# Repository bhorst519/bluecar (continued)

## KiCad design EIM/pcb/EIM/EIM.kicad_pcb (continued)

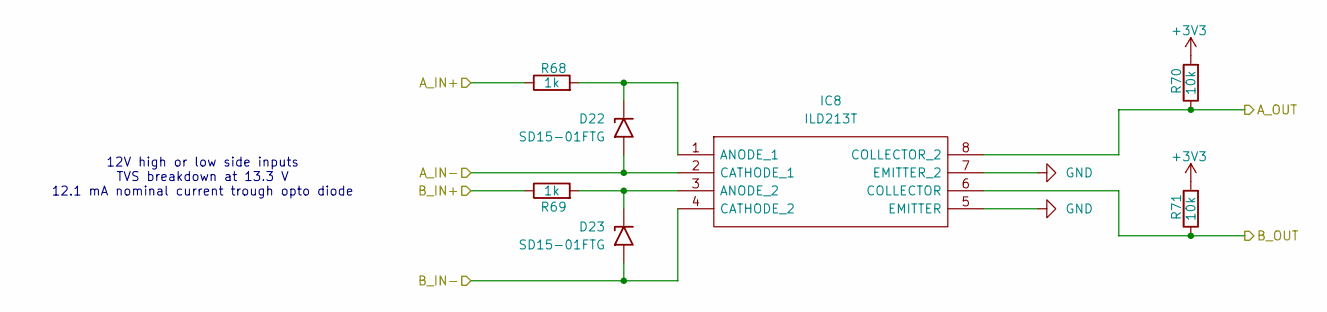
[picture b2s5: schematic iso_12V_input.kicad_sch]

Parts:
D22, D23: SD15-01FTG; D_SOD-323
IC8: ILD213T; SOIC127P610X350-8N; Mouser Part Number 782-ILD213T
R68, R69: 1k; R_0805_2012Metric_Pad1.20x1.40mm_HandSolder
R70, R71: 10k; R_0805_2012Metric_Pad1.20x1.40mm_HandSolder

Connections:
+3V3: R70.2, R71.2; also elsewhere on the board
+12V: R68.1, R69.1; also elsewhere on the board
/5TH: D23.2 (A2), IC8.4 (CATHODE_2); also elsewhere on the board
/5TH_MCU: IC8.6 (COLLECTOR), R71.1; also elsewhere on the board
/6TH: D22.2 (A2), IC8.2 (CATHODE_1); also elsewhere on the board
/6TH_MCU: IC8.8 (COLLECTOR_2), R70.1; also elsewhere on the board
GND: IC8.5 (EMITTER), IC8.7 (EMITTER_2); also elsewhere on the board
unnamed: D22.1 (A1), IC8.1 (ANODE_1), R68.2
unnamed: D23.1 (A1), IC8.3 (ANODE_2), R69.2

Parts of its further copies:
D13, D14, D16, D17, D18, D19, D20, D21, D24, D25, D30, D31: SD15-01FTG; D_SOD-323
IC3, IC5, IC6, IC7, IC9, IC10: ILD213T; SOIC127P610X350-8N; Mouser Part Number 782-ILD213T
R22, R23, R56, R57, R60, R61, R64, R65, R72, R73, R89, R90: 1k; R_0805_2012Metric_Pad1.20x1.40mm_HandSolder
R24, R25, R58, R59, R62, R63, R66, R67, R74, R75, R91, R92: 10k; R_0805_2012Metric_Pad1.20x1.40mm_HandSolder

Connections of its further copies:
+3V3: R24.2, R25.2, R58.2, R59.2, R62.2, R63.2, R66.2, R67.2, R74.2, R75.2, R91.2, R92.2; also elsewhere on the board
+12V: R23.1, R60.1, R61.1, R64.1, R65.1, R72.1, R73.1; also elsewhere on the board
/1ST: D19.2 (A2), IC6.4 (CATHODE_2); also elsewhere on the board
/1ST_MCU: IC6.6 (COLLECTOR), R63.1; also elsewhere on the board
/2ND: D18.2 (A2), IC6.2 (CATHODE_1); also elsewhere on the board
/2ND_MCU: IC6.8 (COLLECTOR_2), R62.1; also elsewhere on the board
/3RD: D21.2 (A2), IC7.4 (CATHODE_2); also elsewhere on the board
/3RD_MCU: IC7.6 (COLLECTOR), R67.1; also elsewhere on the board
/4TH: D20.2 (A2), IC7.2 (CATHODE_1); also elsewhere on the board
/4TH_MCU: IC7.8 (COLLECTOR_2), R66.1; also elsewhere on the board
/FAULT_IND: D24.2 (A2), IC9.2 (CATHODE_1); also elsewhere on the board
/FAULT_IND_MCU: IC9.8 (COLLECTOR_2), R74.1; also elsewhere on the board
/HIGHBEAM: R90.1; also elsewhere on the board
/HIGHBEAM_FEED: R89.1; also elsewhere on the board
/HIGHBEAM_MCU: IC10.6 (COLLECTOR), R92.1; also elsewhere on the board
/LOWBEAM_MCU: IC10.8 (COLLECTOR_2), R91.1; also elsewhere on the board
/NEUTRAL: D14.2 (A2), IC3.4 (CATHODE_2); also elsewhere on the board
/NEUTRAL_MCU: IC3.6 (COLLECTOR), R25.1; also elsewhere on the board
/OIL: D25.2 (A2), IC9.4 (CATHODE_2); also elsewhere on the board
/OIL_P_LOW_MCU: IC9.6 (COLLECTOR), R75.1; also elsewhere on the board
/TACH_MCU: IC3.8 (COLLECTOR_2), R24.1; also elsewhere on the board
/TA_SIG: R22.1; also elsewhere on the board
/TURN_L: R56.1; also elsewhere on the board
/TURN_L_MCU: IC5.8 (COLLECTOR_2), R58.1; also elsewhere on the board
/TURN_R: R57.1; also elsewhere on the board
/TURN_R_MCU: IC5.6 (COLLECTOR), R59.1; also elsewhere on the board
GND: D13.2 (A2), D16.2 (A2), D17.2 (A2), D30.2 (A2), D31.2 (A2), IC3.2 (CATHODE_1), IC3.5 (EMITTER), IC3.7 (EMITTER_2), IC5.2 (CATHODE_1), IC5.4 (CATHODE_2), IC5.5 (EMITTER), IC5.7 (EMITTER_2), IC6.5 (EMITTER), IC6.7 (EMITTER_2), IC7.5 (EMITTER), IC7.7 (EMITTER_2), IC9.5 (EMITTER), IC9.7 (EMITTER_2), IC10.2 (CATHODE_1), IC10.4 (CATHODE_2), IC10.5 (EMITTER), IC10.7 (EMITTER_2); also elsewhere on the board
unnamed: D13.1 (A1), IC3.1 (ANODE_1), R22.2
unnamed: D14.1 (A1), IC3.3 (ANODE_2), R23.2
unnamed: D16.1 (A1), IC5.1 (ANODE_1), R56.2
unnamed: D17.1 (A1), IC5.3 (ANODE_2), R57.2
unnamed: D18.1 (A1), IC6.1 (ANODE_1), R60.2
unnamed: D19.1 (A1), IC6.3 (ANODE_2), R61.2
unnamed: D20.1 (A1), IC7.1 (ANODE_1), R64.2
unnamed: D21.1 (A1), IC7.3 (ANODE_2), R65.2
unnamed: D24.1 (A1), IC9.1 (ANODE_1), R72.2
unnamed: D25.1 (A1), IC9.3 (ANODE_2), R73.2
unnamed: D30.1 (A1), IC10.1 (ANODE_1), R89.2
unnamed: D31.1 (A1), IC10.3 (ANODE_2), R90.2

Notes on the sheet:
12V high or low side inputs TVS breakdown at 13.3 V 12.1 mA nominal current trough opto diode

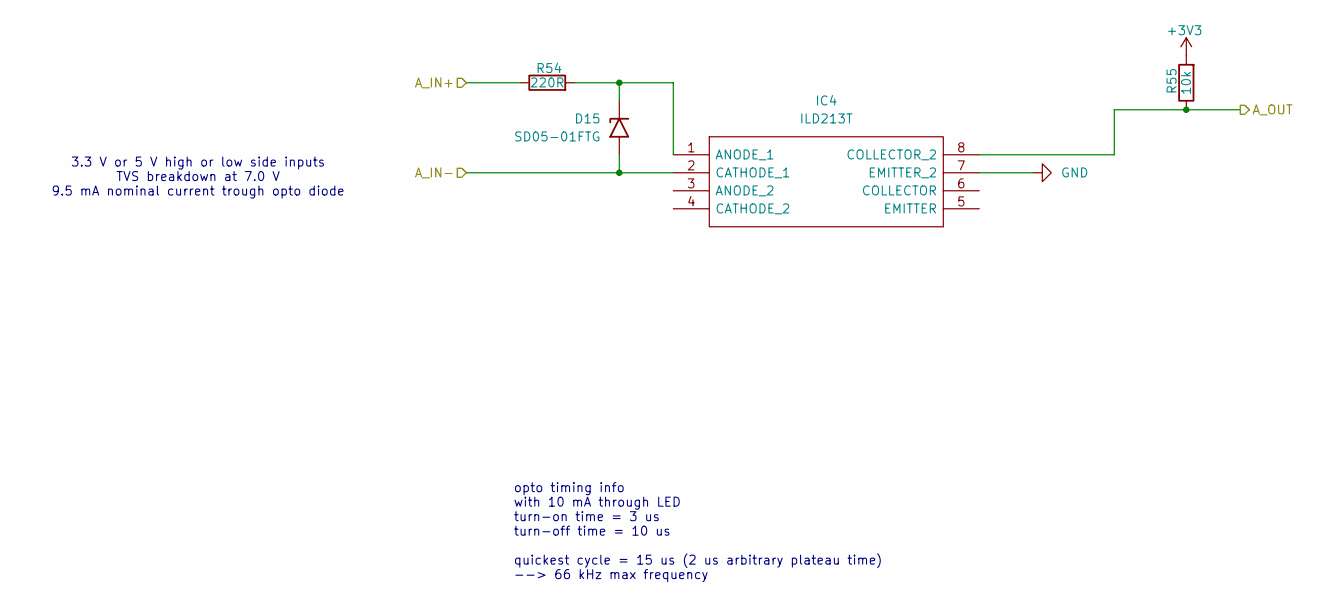
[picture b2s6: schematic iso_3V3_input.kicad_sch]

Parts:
D15: SD05-01FTG; D_SOD-323
IC4: ILD213T; SOIC127P610X350-8N; Mouser Part Number 782-ILD213T
R54: 220R; R_0805_2012Metric_Pad1.20x1.40mm_HandSolder
R55: 10k; R_0805_2012Metric_Pad1.20x1.40mm_HandSolder

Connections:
+3V3: R54.1, R55.2; also elsewhere on the board
/SP_SIG: D15.2 (A2), IC4.2 (CATHODE_1); also elsewhere on the board
/VSS_MCU: IC4.8 (COLLECTOR_2), R55.1; also elsewhere on the board
GND: IC4.7 (EMITTER_2); also elsewhere on the board
unnamed: D15.1 (A1), IC4.1 (ANODE_1), R54.2

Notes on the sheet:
3.3 V or 5 V high or low side inputs TVS breakdown at 7.0 V 9.5 mA nominal current trough opto diode
opto timing info with 10 mA through LED turn-on time = 3 us turn-off time = 10 us quickest cycle = 15 us (2 us arbitrary plateau time) --> 66 kHz max frequency

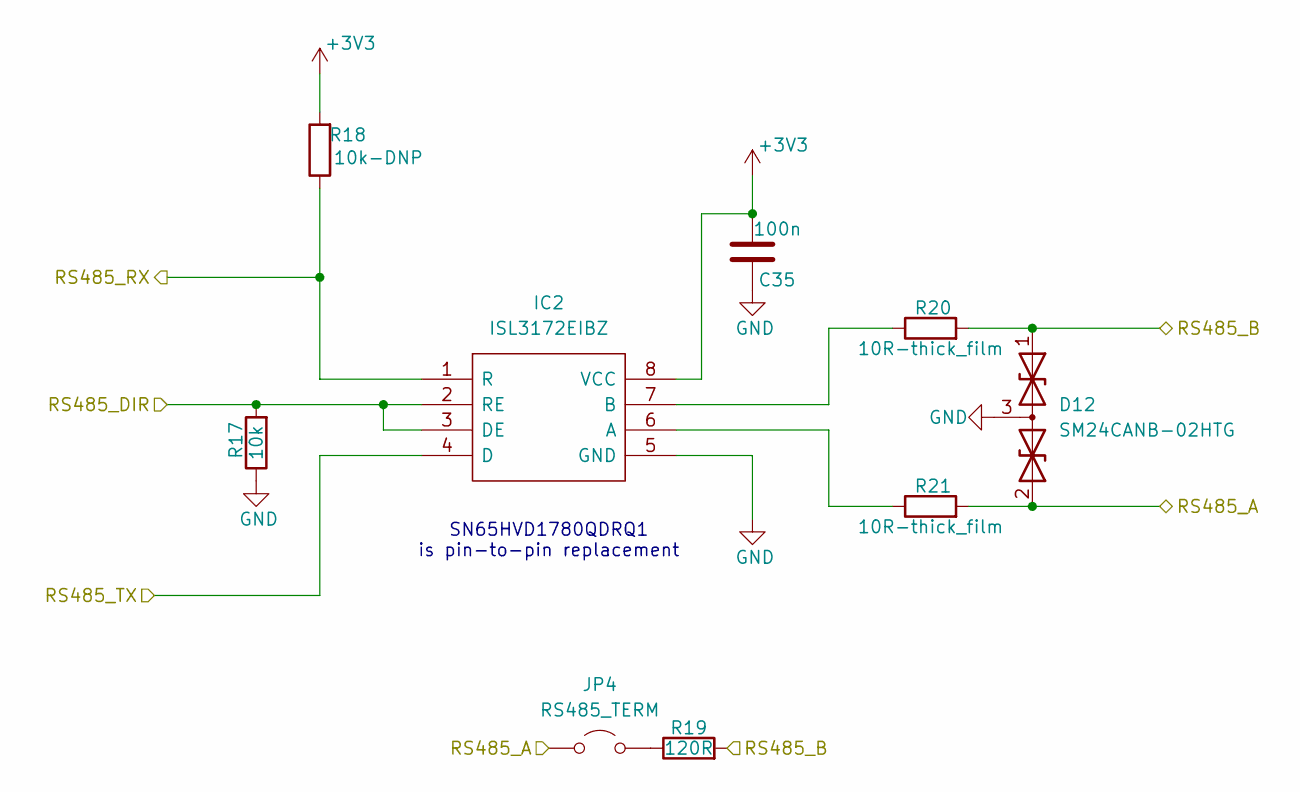
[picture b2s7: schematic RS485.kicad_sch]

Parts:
C35: 100n; C_0805_2012Metric_Pad1.18x1.45mm_HandSolder
D12: SM24CANB-02HTG; SOT-23-3
IC2: ISL3172EIBZ; SOIC-8_3.9x4.9mm_P1.27mm; Mouser Part Number 595-SN65HVD1780QDRQ1
JP4: RS485_TERM; SolderJumper-2_P1.3mm_Bridged_RoundedPad1.0x1.5mm
R17: 10k; R_0805_2012Metric_Pad1.20x1.40mm_HandSolder
R18: 10k-DNP; R_0805_2012Metric_Pad1.20x1.40mm_HandSolder
R19: 120R; R_0805_2012Metric_Pad1.20x1.40mm_HandSolder
R20, R21: 10R-thick_film; R_0805_2012Metric_Pad1.20x1.40mm_HandSolder

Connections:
+3V3: C35.1, IC2.8 (VCC), R18.2; also elsewhere on the board
/RS485_A: D12.2 (A2), JP4.1 (A), R21.2; also elsewhere on the board
/RS485_B: D12.1 (A1), R19.2, R20.2; also elsewhere on the board
/RS485_DIR: IC2.2 (RE), IC2.3 (DE), R17.2; also elsewhere on the board
/RS485_RX: IC2.1 (R), R18.1; also elsewhere on the board
/RS485_TX: IC2.4 (D); also elsewhere on the board
GND: C35.2, D12.3 (common), IC2.5 (GND), R17.1; also elsewhere on the board
unnamed: IC2.6 (A), R21.1
unnamed: IC2.7 (B), R20.1
unnamed: JP4.2 (B), R19.1

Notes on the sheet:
SN65HVD1780QDRQ1 is pin-to-pin replacement

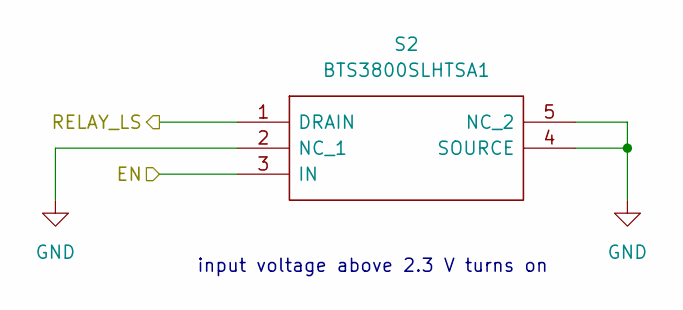
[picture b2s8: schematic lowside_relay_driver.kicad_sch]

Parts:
S2: BTS3800SLHTSA1; Mouser Part Number 726-BTS3800SLHTSA1

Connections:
/HEADLIGHT_RELAY: S2.1 (DRAIN); also elsewhere on the board
/HL_RLY_EN: S2.3 (IN); also elsewhere on the board
GND: S2.2 (NC_1), S2.4 (SOURCE), S2.5 (NC_2); also elsewhere on the board

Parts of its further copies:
S1, S3: BTS3800SLHTSA1; Mouser Part Number 726-BTS3800SLHTSA1

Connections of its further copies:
/LAP_RELAY: S3.1 (DRAIN); also elsewhere on the board
/LAP_RLY_EN: S3.3 (IN); also elsewhere on the board
/MAIN_RLY_COIL_LS: S1.1 (DRAIN); also elsewhere on the board
/MAIN_RLY_EN: S1.3 (IN); also elsewhere on the board
GND: S1.2 (NC_1), S1.4 (SOURCE), S1.5 (NC_2), S3.2 (NC_1), S3.4 (SOURCE), S3.5 (NC_2); also elsewhere on the board

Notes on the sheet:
input voltage above 2.3 V turns on

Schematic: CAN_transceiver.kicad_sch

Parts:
C30: 100n; C_0805_2012Metric_Pad1.18x1.45mm_HandSolder
D8: SM24CANB-02HTG; SOT-23-3
JP2: CAN_TERM; SolderJumper-2_P1.3mm_Open_RoundedPad1.0x1.5mm
R13: 120R; R_0805_2012Metric_Pad1.20x1.40mm_HandSolder
U3: SN65HVD233; SOIC-8_3.9x4.9mm_P1.27mm

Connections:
+3V3: C30.2, U3.3 (VCC); also elsewhere on the board
/CAN1_H: D8.1 (A1), JP2.1 (A), U3.7 (CANH); also elsewhere on the board
/CAN1_L: D8.2 (A2), R13.2, U3.6 (CANL); also elsewhere on the board
/CAN1_RX: U3.4 (R); also elsewhere on the board
/CAN1_TX: U3.1 (D); also elsewhere on the board
GND: C30.1, D8.3 (common), U3.2 (GND), U3.5 (LBK), U3.8 (Rs); also elsewhere on the board
unnamed: JP2.2 (B), R13.1

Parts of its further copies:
C31: 100n; C_0805_2012Metric_Pad1.18x1.45mm_HandSolder
D9: SM24CANB-02HTG; SOT-23-3
JP3: CAN_TERM; SolderJumper-2_P1.3mm_Open_RoundedPad1.0x1.5mm
R14: 120R; R_0805_2012Metric_Pad1.20x1.40mm_HandSolder
U4: SN65HVD233; SOIC-8_3.9x4.9mm_P1.27mm

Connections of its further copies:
+3V3: C31.2, U4.3 (VCC); also elsewhere on the board
/CAN2_H: D9.1 (A1), JP3.1 (A), U4.7 (CANH); also elsewhere on the board
/CAN2_L: D9.2 (A2), R14.2, U4.6 (CANL); also elsewhere on the board
/CAN2_RX: U4.4 (R); also elsewhere on the board
/CAN2_TX: U4.1 (D); also elsewhere on the board
GND: C31.1, D9.3 (common), U4.2 (GND), U4.5 (LBK), U4.8 (Rs); also elsewhere on the board
unnamed: JP3.2 (B), R14.1

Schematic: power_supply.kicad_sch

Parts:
C23, C24: 10u/X7R/50V; C_1206_3216Metric_Pad1.33x1.80mm_HandSolder
C25, C26, C27: 100n; C_0805_2012Metric_Pad1.18x1.45mm_HandSolder
C28, C29: 22u/16V; CP_Elec_4x5.8
D6: SK22; D_SMB
D7: SMBJ15A; D_SMB
F3, F4: 2920L260/33DR; Fuse_2920_7451Metric
FB2: 220ohm / 10MHZ; L_0805_2012Metric_Pad1.15x1.40mm_HandSolder
L1: 3.6uH; L_Bourns-SRN8040_8x8.15mm
U2: AP63203WU; TSOT-23-6

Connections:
+3V3: C27.1, C28.1, C29.1, L1.2, U2.1 (FB); also elsewhere on the board
+12V: C23.2, C24.2, C25.1, F3.2, F4.1, U2.2 (EN), U2.3 (IN); also elsewhere on the board
/KEYSWITCH_RTN: D6.2 (A); also elsewhere on the board
/Power Supply/3V3_BUCK_BS: C26.2, U2.6 (BST)
/Power Supply/3V3_BUCK_OUT: C26.1, L1.1, U2.5 (SW)
/Power Supply/12V_DIODE: D6.1 (K), D7.1 (A1), F3.1
/Power Supply/SERVO_FUSED: F4.2, FB2.1
/SERVO_12V: FB2.2; also elsewhere on the board
GND: C23.1, C24.1, C25.2, C27.2, C28.2, C29.2, D7.2 (A2), U2.4 (GND); also elsewhere on the board

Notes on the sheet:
100n caps are 50V
2.6 A hold 5 A trip polyfuse
caps dereated to 50% at 12 V DC bias, so two are used

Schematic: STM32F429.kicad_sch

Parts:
C1, C2, C5, C6, C7, C8, C9, C10, C11, C12, C13, C14, C15, C16, C17, C18, C19, C21: 100n; C_0805_2012Metric_Pad1.18x1.45mm_HandSolder
C3, C4: 2.2u/X7R; C_1206_3216Metric_Pad1.33x1.80mm_HandSolder
C20: 10u/X7R/50V; C_1206_3216Metric_Pad1.33x1.80mm_HandSolder
C22: 1u; C_0805_2012Metric_Pad1.18x1.45mm_HandSolder
FB1: 600ohm; L_0805_2012Metric_Pad1.15x1.40mm_HandSolder
J7: FTSH-107-01-F-DV-K; FTSH-107-XX-YYY-DV-K; Mouser Part Number 200-FTSH10701FDVK
J8: SWD; PinHeader_1x06_P2.54mm_Vertical
JP1: RESET; SolderJumper-3_P1.3mm_Bridged12_RoundedPad1.0x1.5mm
R8: 10k; R_0805_2012Metric_Pad1.20x1.40mm_HandSolder
R9, R11, R12: 0R; R_0805_2012Metric_Pad1.20x1.40mm_HandSolder
R10: 120R; R_0805_2012Metric_Pad1.20x1.40mm_HandSolder
SW1: BOOT; SW_SPST_PTS645
SW2: RESET; SW_SPST_PTS645
U1: STM32F429ZITx; LQFP-144_20x20mm_P0.5mm
X1: ASE-8.000MHz; Oscillator_SMD_Abracon_ASE-4Pin_3.2x2.5mm
X2: ECS-327-32.768kHz; Oscillator_SMD_Abracon_ASE-4Pin_3.2x2.5mm

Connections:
+3V3: C1.1, C5.1, C6.1, C7.1, C8.1, C9.1, C10.1, C11.1, C12.1, C13.1, C14.1, C15.1, C16.1, C17.1, C18.1, C19.1, C20.1, FB1.1, J7.3, J8.1, SW1.1, U1.6 (VBAT), U1.17 (VDD), U1.30 (VDD), U1.39 (VDD), U1.52 (VDD), U1.62 (VDD), U1.72 (VDD), U1.84 (VDD), U1.95 (VDD), U1.108 (VDD), U1.121 (VDD), U1.131 (VDD), U1.143 (PDR_ON), U1.144 (VDD), X1.1 (EN), X1.4 (Vdd), X2.1 (EN), X2.4 (Vdd); also elsewhere on the board
/1ST_MCU: U1.65 (PE12); also elsewhere on the board
/2ND_MCU: U1.64 (PE11); also elsewhere on the board
/3RD_MCU: U1.63 (PE10); also elsewhere on the board
/4TH_MCU: U1.60 (PE9); also elsewhere on the board
/5TH_MCU: U1.59 (PE8); also elsewhere on the board
/6TH_MCU: U1.58 (PE7); also elsewhere on the board
/12V_ADC: U1.47 (PB1); also elsewhere on the board
/BRAKE_LIGHT_EN: U1.18 (PF6); also elsewhere on the board
/BRAKE_LIGHT_I_SEN: U1.35 (PA1); also elsewhere on the board
/CAN1_RX: U1.103 (PA11); also elsewhere on the board
/CAN1_TX: U1.104 (PA12); also elsewhere on the board
/CAN2_RX: U1.73 (PB12); also elsewhere on the board
/CAN2_TX: U1.74 (PB13); also elsewhere on the board
/ENG_12V_ADC: U1.37 (PA3); also elsewhere on the board
/ENG_ON_EN: U1.14 (PF4); also elsewhere on the board
/ENG_ON_RLY_I_SEN: U1.26 (PC0); also elsewhere on the board
/ENG_START_EN: U1.15 (PF5); also elsewhere on the board
/ENG_START_RLY_I_SEN: U1.36 (PA2); also elsewhere on the board
/ENG_TEMP_ADC: U1.42 (PA6); also elsewhere on the board
/EXTRA_ADC: U1.46 (PB0); also elsewhere on the board
/FAULT_IND_MCU: U1.45 (PC5); also elsewhere on the board
/FUEL_LOW_ADC: U1.41 (PA5); also elsewhere on the board
/FUEL_LVL_ADC: U1.40 (PA4); also elsewhere on the board
/HIGHBEAM_EN: U1.19 (PF7); also elsewhere on the board
/HIGHBEAM_I_SEN: U1.34 (PA0); also elsewhere on the board
/HIGHBEAM_MCU: U1.55 (PF15); also elsewhere on the board
/HL_RLY_EN: U1.66 (PE13); also elsewhere on the board
/HORN_EN: U1.22 (PF10); also elsewhere on the board
/HORN_I_SEN: U1.27 (PC1); also elsewhere on the board
/I2C_SCL: U1.136 (PB6); also elsewhere on the board
/I2C_SDA: U1.137 (PB7); also elsewhere on the board
/KLINE_EN: U1.12 (PF2); also elsewhere on the board
/KLINE_RX: U1.102 (PA10); also elsewhere on the board
/KLINE_TX: U1.101 (PA9); also elsewhere on the board
/LAP_RLY_EN: U1.67 (PE14); also elsewhere on the board
/LED1: U1.139 (PB8); also elsewhere on the board
/LED2_B: U1.140 (PB9); also elsewhere on the board
/LED2_G: U1.82 (PD13); also elsewhere on the board
/LED2_R: U1.81 (PD12); also elsewhere on the board
/LOWBEAM_MCU: U1.54 (PF14); also elsewhere on the board
/L_TURN_SIG_EN: U1.20 (PF8); also elsewhere on the board
/L_TURN_SIG_I_SEN: U1.29 (PC3); also elsewhere on the board
/MAIN_RLY_EN: U1.13 (PF3); also elsewhere on the board
/NEUTRAL_MCU: U1.53 (PF13); also elsewhere on the board
/OIL_P_LOW_MCU: U1.49 (PF11); also elsewhere on the board
/PB2/BOOT1: U1.48 (PB2); also elsewhere on the board
/RS485_DIR: U1.118 (PD4); also elsewhere on the board
/RS485_RX: U1.122 (PD6); also elsewhere on the board
/RS485_TX: U1.119 (PD5); also elsewhere on the board
/R_TURN_SIG_EN: U1.21 (PF9); also elsewhere on the board
/R_TURN_SIG_I_SEN: U1.28 (PC2); also elsewhere on the board
/SERVO_12V_ADC: U1.43 (PA7); also elsewhere on the board
/SPI2_MISO: U1.75 (PB14); also elsewhere on the board
/SPI2_MOSI: U1.76 (PB15); also elsewhere on the board
/SPI2_SCK: U1.117 (PD3); also elsewhere on the board
/STM32F429/GND-detect: J7.11, R10.2
/STM32F429/JRST: JP1.3 (B), U1.134 (PB4)
/STM32F429/JTDI: J7.10, U1.110 (PA15)
/STM32F429/JTDO-SWO: J7.8, J8.6, U1.133 (PB3)
/STM32F429/JTICK-SWCLK: J7.6, J8.2, U1.109 (PA14)
/STM32F429/JTMS-SWDIO: J7.4, J8.4, U1.105 (PA13)
/STM32F429/NRST: C2.2, JP1.1 (A), SW2.2, U1.25 (NRST)
/STM32F429/OSC32_IN: R12.2, U1.8 (PC14)
/STM32F429/OSC32_OUT: U1.9 (PC15)
/STM32F429/OSC_IN: R11.2, U1.23 (PH0)
/STM32F429/OSC_OUT: U1.24 (PH1)
/STM32F429/RESET: J7.12, J8.5, JP1.2 (C)
/STM32F429/USART3_RX: J7.13, U1.70 (PB11)
/STM32F429/USART3_TX: J7.14, U1.69 (PB10)
/TACH_MCU: U1.50 (PF12); also elsewhere on the board
/TURN_L_MCU: U1.56 (PG0); also elsewhere on the board
/TURN_R_MCU: U1.57 (PG1); also elsewhere on the board
/UART4_RX: U1.112 (PC11); also elsewhere on the board
/UART4_TX: U1.111 (PC10); also elsewhere on the board
/VSS_MCU: U1.44 (PC4); also elsewhere on the board
GND: C2.1, C3.1, C4.1, C5.2, C6.2, C7.2, C8.2, C9.2, C10.2, C11.2, C12.2, C13.2, C14.2, C15.2, C16.2, C17.2, C18.2, C19.2, C20.2, C21.2, C22.2, J7.5, J7.7, J8.3, R8.1, R10.1, SW2.1, U1.16 (VSS), U1.31 (VSSA), U1.38 (VSS), U1.51 (VSS), U1.61 (VSS), U1.83 (VSS), U1.94 (VSS), U1.107 (VSS), U1.120 (VSS), U1.130 (VSS), X1.2 (GND), X2.2 (GND); also elsewhere on the board
unnamed: C1.2, R8.2, SW1.2, U1.138 (BOOT0)
unnamed: C3.2, U1.71 (VCAP_1)
unnamed: C4.2, U1.106 (VCAP_2)
unnamed: R9.2, U1.32 (VREF+)
unnamed: R11.1, X1.3 (OUT)
unnamed: R12.1, X2.3 (OUT)
VDDA: C21.1, C22.1, FB1.2, R9.1, U1.33 (VDDA)

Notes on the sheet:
Bypass caps for pins 17, 30, 39, 52, 62, 72, 84, 95, 108, 121, 131, 144
Bypass cap for VBAT
Matches STLINK V2
STDC14 JTAG/SWD
Pins 13 & 14 to STLINK virtual comm port (VCP)

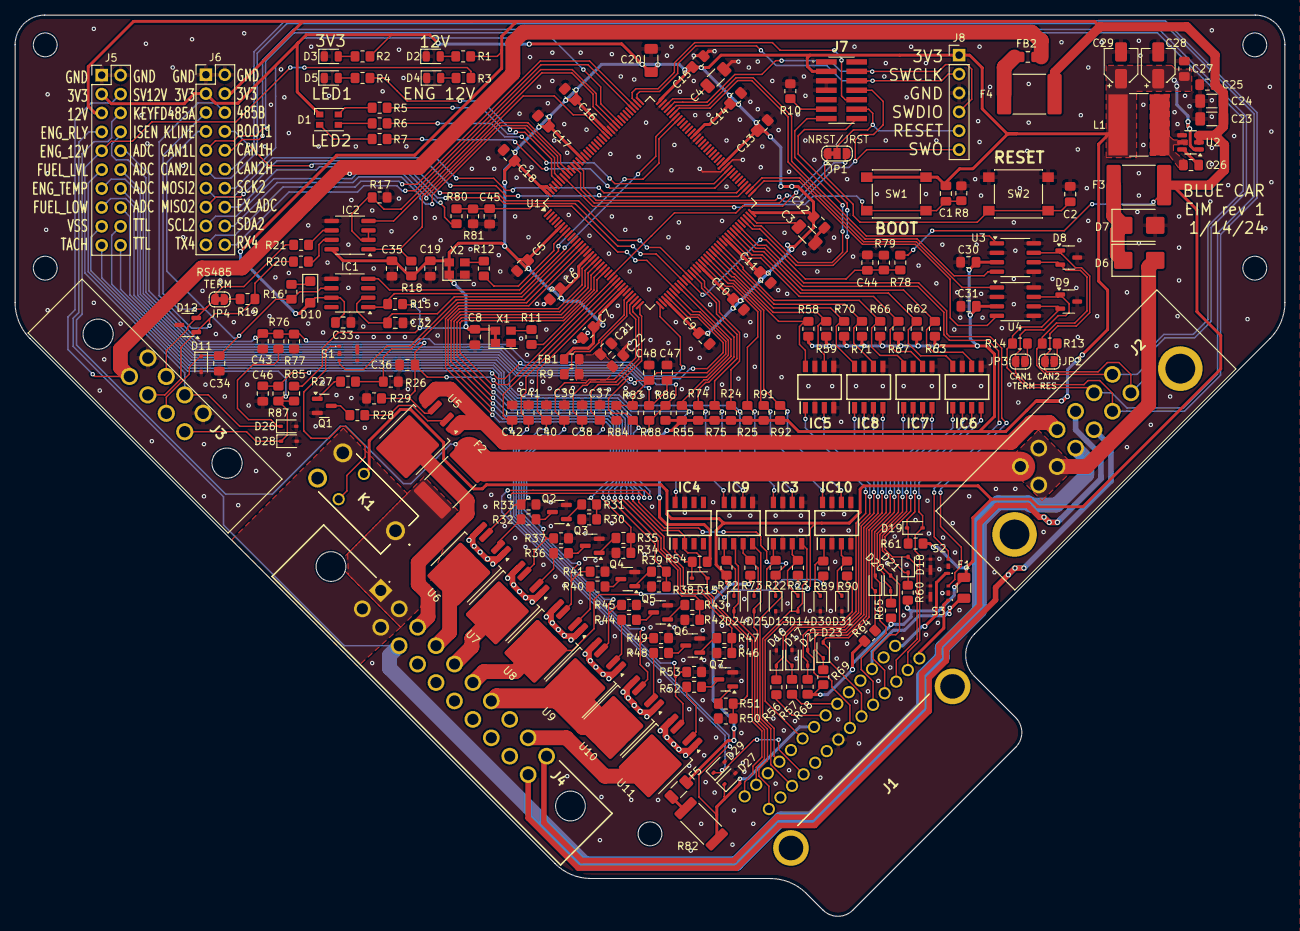
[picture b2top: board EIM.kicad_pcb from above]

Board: 2 copper layers, 170.6 x 121.1 mm, 227 parts (0 on the bottom side), 187 nets.

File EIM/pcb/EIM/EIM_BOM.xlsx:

Id | Designator | Footprint | Quantity | Designation | Supplier and ref | Column1 | _1
1 | D15,D29,D28 | D_SOD-323 | 3 | SD05-01FTG
2 | D19,D25,D21,D14,D11,D24,D16,D13,D31,D17,D30,D20,D18,D22,D23 | D_SOD-323 | 15 | SD15-01FTG
3 | J1 | MX34028NF2 | 1 | MX34028NF2
4 | R53,R27,R47,R49,R31,R51,R37,R33,R43,R29,R45,R41,R39,R35 | R_0805_2012Metric_Pad1.20x1.40mm_HandSolder | 14 | 470R
5 | R15,R18 | R_0805_2012Metric_Pad1.20x1.40mm_HandSolder | 2 | 10k-DNP
6 | IC3,IC10,IC9,IC7,IC5,IC4,IC6,IC8 | SOIC127P610X350-8N | 8 | ILD213T
7 | U8,U9,U7,U5,U6,U10,U11 | TO-252-4 | 7 | BTS6142D
8 | J5 | PinHeader_2x10_P2.54mm_Vertical | 1 | DEBUG1
9 | R38,R25,R62,R24,R42,R46,R71,R50,R70,R34,R74,R30,R8,R26,R66,R17,R75,R91,R59,R58,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 | R_0805_2012Metric_Pad1.20x1.40mm_HandSolder | 24 | 10k
10 | C7,C16,C38,C41,C27,C26,C18,C32,C46,C37,C15,C45,C48,C47,C12,C19,C39,C14,C5,C8,C3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 | C_0805_2012Metric_Pad1.18x1.45mm_HandSolder | 39 | 100n
11 | R4,R23,R61,R73,R64,R89,R68,R56,R72,R65,R87,R90,R57,R2,R69,R88,R16,R22,R60 | R_0805_2012Metric_Pad1.20x1.40mm_HandSolder | 19 | 1k
12 | Q5,Q2,Q1,Q6,Q4,Q3,Q7 | SOT-23 | 7 | BSS138
13 | JP2,JP3 | SolderJumper-2_P1.3mm_Open_RoundedPad1.0x1.5mm | 2 | CAN_TERM
14 | D2 | LED_0805_2012Metric | 1 | RED
15 | SW2 | SW_SPST_PTS645 | 1 | RESET
16 | D10 | D_SMF | 1 | VS-1EFH01-M3/I
17 | K1 | G8N1LASDC12 | 1 | G8N-1L-AS_DC12
18 | S3,S2,S1 | BTS3800SLHTSA1 | 3 | BTS3800SLHTSA1
19 | FB2 | L_0805_2012Metric_Pad1.15x1.40mm_HandSolder | 1 | 220ohm / 10MHZ
20 | D5 | LED_0805_2012Metric | 1 | YELLOW
21 | R19,R14,R13 | R_0805_2012Metric_Pad1.20x1.40mm_HandSolder | 3 | 120R
22 | R78,R83,R80,R86,R76 | R_0805_2012Metric_Pad1.20x1.40mm_HandSolder | 5 | 3k6, 0.5%
23 | C29,C28 | CP_Elec_4x5.8 | 2 | 22u/16V
24 | R12,R32,R44,R40,R52,R11,R9,R28,R36,R48 | R_0805_2012Metric_Pad1.20x1.40mm_HandSolder | 10 | 0R
25 | C24,C20,C23 | C_1206_3216Metric_Pad1.33x1.80mm_HandSolder | 3 | 10u/X7R/50V
26 | F1 | Fuse_1206_3216Metric | 1 | 1206L035/16YR
27 | F2 | Fuse_2920_7451Metric | 1 | 2920L600/16MR
28 | R20,R21 | R_0805_2012Metric_Pad1.20x1.40mm_HandSolder | 2 | 10R-thick_film
29 | F5 | Fuse_1206_3216Metric | 1 | 1206L010/60WR
30 | R84,R79,R81,R77 | R_0805_2012Metric_Pad1.20x1.40mm_HandSolder | 4 | 1k, 0.5%
31 | U1 | LQFP-144_20x20mm_P0.5mm | 1 | STM32F429ZITx
32 | J7 | FTSH-107-XX-YYY-DV-K | 1 | FTSH-107-01-F-DV-K
33 | R82 | R_2512_6332Metric | 1 | 220R, 1W
34 | R6,R54,R5 | R_0805_2012Metric_Pad1.20x1.40mm_HandSolder | 3 | 220R
35 | X1 | Oscillator_SMD_Abracon_ASE-4Pin_3.2x2.5mm | 1 | ASE-8.000MHz
36 | D4 | LED_0805_2012Metric | 1 | DEEP RED
37 | D6 | D_SMB | 1 | SK22
38 | FB1 | L_0805_2012Metric_Pad1.15x1.40mm_HandSolder | 1 | 600ohm
39 | IC2 | SOIC-8_3.9x4.9mm_P1.27mm | 1 | ISL3172EIBZ
40 | U4,U3 | SOIC-8_3.9x4.9mm_P1.27mm | 2 | SN65HVD233
41 | D26,D27 | D_SOD-323 | 2 | SD12-01FTG
42 | D12,D8,D9 | SOT-23-3 | 3 | SM24CANB-02HTG
43 | R85 | R_0805_2012Metric_Pad1.20x1.40mm_HandSolder | 1 | 220R, 0.5%
44 | J6 | PinHeader_2x10_P2.54mm_Vertical | 1 | DEBUG2
45 | R3,R1 | R_0805_2012Metric_Pad1.20x1.40mm_HandSolder | 2 | 15k
46 | C4,C3 | C_1206_3216Metric_Pad1.33x1.80mm_HandSolder | 2 | 2.2u/X7R
47 | J8 | PinHeader_1x06_P2.54mm_Vertical | 1 | SWD
48 | X2 | Oscillator_SMD_Abracon_ASE-4Pin_3.2x2.5mm | 1 | ECS-327-32.768kHz
49 | L1 | L_Bourns-SRN8040_8x8.15mm | 1 | 3.6uH
50 | IC1 | SOIC-8_3.9x4.9mm_P1.27mm | 1 | TLIN1027DRQ1
51 | J4 | 348302001 | 1 | 34830-2001
52 | C22 | C_0805_2012Metric_Pad1.18x1.45mm_HandSolder | 1 | 1u
53 | R7 | R_0805_2012Metric_Pad1.20x1.40mm_HandSolder | 1 | 1k5
54 | F3,F4 | Fuse_2920_7451Metric | 2 | 2920L260/33DR
55 | J3 | 348300801 | 1 | 34830-0801
56 | C34 | C_0805_2012Metric_Pad1.18x1.45mm_HandSolder | 1 | 220p
57 | SW1 | SW_SPST_PTS645 | 1 | BOOT
58 | D7 | D_SMB | 1 | SMBJ15A
59 | JP4 | SolderJumper-2_P1.3mm_Bridged_RoundedPad1.0x1.5mm | 1 | RS485_TERM
60 | D3 | LED_0805_2012Metric | 1 | GREEN
61 | R10 | R_0805_2012Metric_Pad1.20x1.40mm_HandSolder | 1 | 100R
62 | U2 | TSOT-23-6 | 1 | AP63203WU
63 | J2 | 367831201 | 1 | 36783-1201
64 | D1 | LED_Cree-PLCC4_3.2x2.8mm_CCW | 1 | CLV1L-FKB

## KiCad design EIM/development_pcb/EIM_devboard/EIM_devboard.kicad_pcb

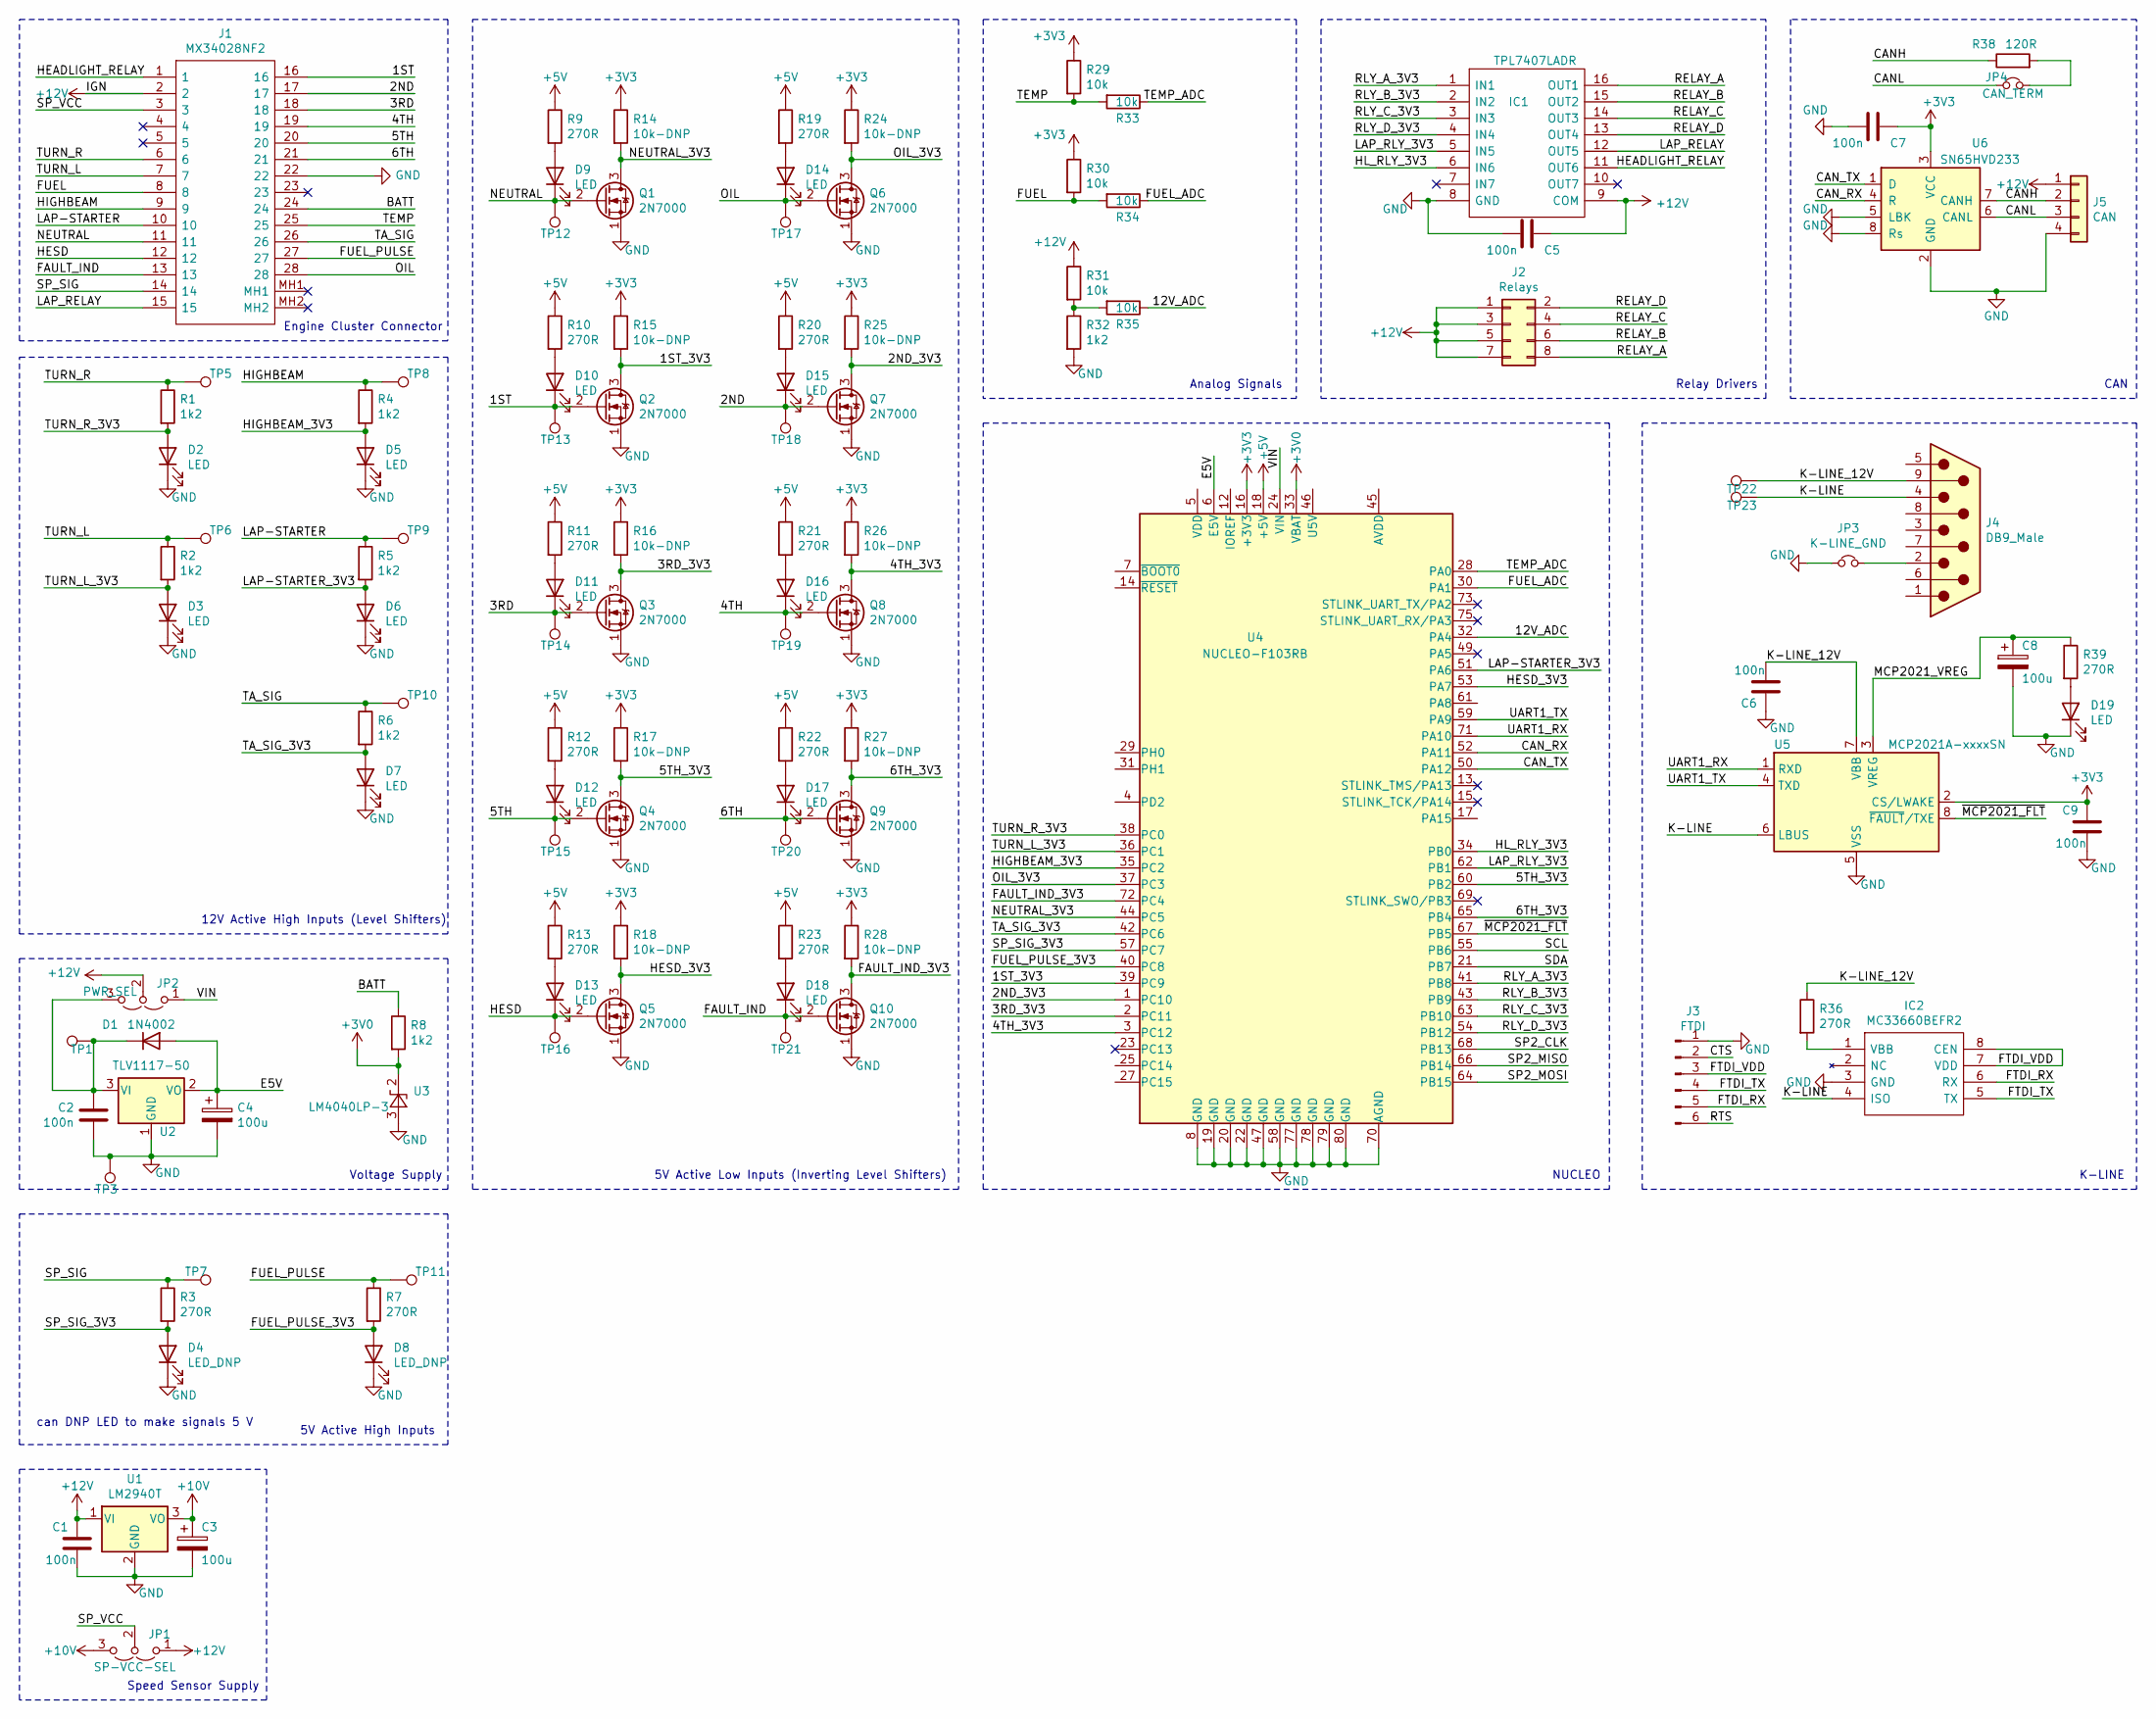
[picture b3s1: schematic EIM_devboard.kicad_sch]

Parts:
C1, C2, C5, C6, C7, C9: 100n; C_Disc_D6.0mm_W2.5mm_P5.00mm
C3, C4, C8: 100u; CP_Radial_D5.0mm_P2.00mm
D1: 1N4002; D_DO-41_SOD81_P10.16mm_Horizontal
D2, D3, D5, D6, D7, D9, D10, D11, D12, D13, D14, D15, D16, D17, D18, D19: LED; LED_D3.0mm
D4, D8: LED_DNP; LED_D3.0mm
IC1: TPL7407LADR; SOIC127P600X175-16N; Mouser Part Number 595-TPL7407LADR
IC2: MC33660BEFR2; SOIC127P600X175-8N; Mouser Part Number 841-MC33660BEFR2
J1: MX34028NF2; Mouser Part Number 656-MX34028NF2
J2: Relays; TerminalBlock_4Ucon_1x08_P3.50mm_Horizontal
J3: FTDI; PinSocket_1x06_P2.54mm_Vertical
J4: DB9_Male; L717SDE09P1ACH4R
J5: CAN; TerminalBlock_4Ucon_1x04_P3.50mm_Horizontal
JP1: SP-VCC-SEL; PinHeader_1x03_P2.54mm_Vertical
JP2: PWR_SEL; PinHeader_1x03_P2.54mm_Vertical
JP3: K-LINE_GND; PinSocket_1x02_P2.54mm_Vertical
JP4: CAN_TERM; PinSocket_1x02_P2.54mm_Vertical
Q1, Q2, Q3, Q4, Q5, Q6, Q7, Q8, Q9, Q10: 2N7000; TO-92_Inline
R1, R2, R4, R5, R6, R8, R32: 1k2; R_Axial_DIN0204_L3.6mm_D1.6mm_P7.62mm_Horizontal
R3, R7, R9, R10, R11, R12, R13, R19, R20, R21, R22, R23, R36, R39: 270R; R_Axial_DIN0204_L3.6mm_D1.6mm_P7.62mm_Horizontal
R14, R15, R16, R17, R18, R24, R25, R26, R27, R28: 10k-DNP; R_Axial_DIN0204_L3.6mm_D1.6mm_P7.62mm_Horizontal
R29, R30, R31, R33, R34, R35: 10k; R_Axial_DIN0204_L3.6mm_D1.6mm_P7.62mm_Horizontal
R38: 120R; R_Axial_DIN0204_L3.6mm_D1.6mm_P7.62mm_Horizontal
TP1, TP3, TP5, TP6, TP7, TP8, TP9, TP10, TP11, TP12, TP13, TP14, TP15, TP16, TP17, TP18, TP19, TP20, TP21, TP22, TP23: TP; TestPoint_Loop_D2.60mm_Drill1.6mm_Beaded
U1: LM2940T; TO-220-3_Vertical
U2: TLV1117-50; SOT-223-3_TabPin2
U3: LM4040LP-3; TO-92_Inline
U4: NUCLEO-F103RB; ST_Morpho_Connector_64
U5: MCP2021A-xxxxSN; SOIC-8_3.9x4.9mm_P1.27mm
U6: SN65HVD233; SOIC-8_3.9x4.9mm_P1.27mm

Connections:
+3V0: R8.2, U3.2 (K), U4.33 (VBAT)
+3V3: C7.2, C9.2, R14.1, R15.1, R16.1, R17.1, R18.1, R24.1, R25.1, R26.1, R27.1, R28.1, R29.1, R30.1, U4.16 (+3V3), U5.2 (CS/LWAKE), U6.3 (VCC)
+5V: R9.1, R10.1, R11.1, R12.1, R13.1, R19.1, R20.1, R21.1, R22.1, R23.1, U4.18 (+5V)
+10V: C3.1, JP1.3 (B), U1.3 (VO)
+12V: C1.2, C5.2, IC1.9 (COM), J1.2, J2.1, J2.3, J2.5, J2.7, J5.1, JP1.1 (A), JP2.2 (C), R31.1, U1.1 (VI)
/1ST: D10.1 (K), J1.16, Q2.2 (G), TP13.1
/1ST_3V3: Q2.3 (D), R15.2, U4.39 (PC9)
/2ND: D15.1 (K), J1.17, Q7.2 (G), TP18.1
/2ND_3V3: Q7.3 (D), R25.2, U4.1 (PC10)
/3RD: D11.1 (K), J1.18, Q3.2 (G), TP14.1
/3RD_3V3: Q3.3 (D), R16.2, U4.2 (PC11)
/4TH: D16.1 (K), J1.19, Q8.2 (G), TP19.1
/4TH_3V3: Q8.3 (D), R26.2, U4.3 (PC12)
/5TH: D12.1 (K), J1.20, Q4.2 (G), TP15.1
/5TH_3V3: Q4.3 (D), R17.2, U4.60 (PB2)
/6TH: D17.1 (K), J1.21, Q9.2 (G), TP20.1
/6TH_3V3: Q9.3 (D), R27.2, U4.65 (PB4)
/12V_ADC: R35.1, U4.32 (PA4)
/BATT: J1.24, R8.1
/CANH: J5.2, R38.1, U6.7 (CANH)
/CANL: J5.3, JP4.1, U6.6 (CANL)
/CAN_RX: U4.52 (PA11), U6.4 (R)
/CAN_TX: U4.50 (PA12), U6.1 (D)
/CTS: J3.2
/E5V: C4.1, D1.2 (A), U2.2 (VO), U4.6 (E5V)
/FAULT_IND: D18.1 (K), J1.13, Q10.2 (G), TP21.1
/FAULT_IND_3V3: Q10.3 (D), R28.2, U4.72 (PC4)
/FTDI_RX: IC2.6 (RX), J3.5
/FTDI_TX: IC2.5 (TX), J3.4
/FTDI_VDD: IC2.7 (VDD), IC2.8 (CEN), J3.3
/FUEL: J1.8, R30.2, R34.2
/FUEL_ADC: R34.1, U4.30 (PA1)
/FUEL_PULSE: J1.27, R7.1, TP11.1
/FUEL_PULSE_3V3: D8.2 (A), R7.2, U4.40 (PC8)
/HEADLIGHT_RELAY: IC1.11 (OUT6), J1.1
/HESD: D13.1 (K), J1.12, Q5.2 (G), TP16.1
/HESD_3V3: Q5.3 (D), R18.2, U4.53 (PA7)
/HIGHBEAM: J1.9, R4.1, TP8.1
/HIGHBEAM_3V3: D5.2 (A), R4.2, U4.35 (PC2)
/HL_RLY_3V3: IC1.6 (IN6), U4.34 (PB0)
/K-LINE: IC2.4 (ISO), J4.4, TP23.1, U5.6 (LBUS)
/K-LINE_12V: C6.1, J4.9, R36.1, TP22.1, U5.7 (VBB)
/LAP-STARTER: J1.10, R5.1, TP9.1
/LAP-STARTER_3V3: D6.2 (A), R5.2, U4.51 (PA6)
/LAP_RELAY: IC1.12 (OUT5), J1.15
/LAP_RLY_3V3: IC1.5 (IN5), U4.62 (PB1)
/MCP2021_VREG: C8.1, R39.1, U5.3 (VREG)
/NEUTRAL: D9.1 (K), J1.11, Q1.2 (G), TP12.1
/NEUTRAL_3V3: Q1.3 (D), R14.2, U4.44 (PC5)
/OIL: D14.1 (K), J1.28, Q6.2 (G), TP17.1
/OIL_3V3: Q6.3 (D), R24.2, U4.37 (PC3)
/RELAY_A: IC1.16 (OUT1), J2.8
/RELAY_B: IC1.15 (OUT2), J2.6
/RELAY_C: IC1.14 (OUT3), J2.4
/RELAY_D: IC1.13 (OUT4), J2.2
/RLY_A_3V3: IC1.1 (IN1), U4.41 (PB8)
/RLY_B_3V3: IC1.2 (IN2), U4.43 (PB9)
/RLY_C_3V3: IC1.3 (IN3), U4.63 (PB10)
/RLY_D_3V3: IC1.4 (IN4), U4.54 (PB12)
/RTS: J3.6
/SCL: U4.55 (PB6)
/SDA: U4.21 (PB7)
/SP2_CLK: U4.68 (PB13)
/SP2_MISO: U4.66 (PB14)
/SP2_MOSI: U4.64 (PB15)
/SP_SIG: J1.14, R3.1, TP7.1
/SP_SIG_3V3: D4.2 (A), R3.2, U4.57 (PC7)
/SP_VCC: J1.3, JP1.2 (C)
/TA_SIG: J1.26, R6.1, TP10.1
/TA_SIG_3V3: D7.2 (A), R6.2, U4.42 (PC6)
/TEMP: J1.25, R29.2, R33.2
/TEMP_ADC: R33.1, U4.28 (PA0)
/TURN_L: J1.7, R2.1, TP6.1
/TURN_L_3V3: D3.2 (A), R2.2, U4.36 (PC1)
/TURN_R: J1.6, R1.1, TP5.1
/TURN_R_3V3: D2.2 (A), R1.2, U4.38 (PC0)
/UART1_RX: U4.71 (PA10), U5.1 (RXD)
/UART1_TX: U4.59 (PA9), U5.4 (TXD)
/VIN: JP2.1 (A), U4.24 (VIN)
/~MCP2021_FLT: U4.67 (PB5), U5.8 (~FAULT/TXE)
GND: C1.1, C2.1, C3.2, C4.2, C5.1, C6.2, C7.1, C8.2, C9.1, D2.1 (K), D3.1 (K), D4.1 (K), D5.1 (K), D6.1 (K), D7.1 (K), D8.1 (K), D19.1 (K), IC1.8 (GND), IC2.3 (GND), J1.22, J3.1, J5.4, JP3.1, Q1.1 (S), Q2.1 (S), Q3.1 (S), Q4.1 (S), Q5.1 (S), Q6.1 (S), Q7.1 (S), Q8.1 (S), Q9.1 (S), Q10.1 (S), R32.2, TP3.1, U1.2 (GND), U2.1 (GND), U3.3 (A), U4.8 (GND), U4.19 (GND), U4.20 (GND), U4.22 (GND), U4.47 (GND), U4.58 (GND), U4.70 (AGND), U4.77 (GND), U4.78 (GND), U4.79 (GND), U4.80 (GND), U5.5 (VSS), U6.2 (GND), U6.5 (LBK), U6.8 (Rs)
unnamed: C2.2, D1.1 (K), JP2.3 (B), TP1.1, U2.3 (VI)
unnamed: D9.2 (A), R9.2
unnamed: D10.2 (A), R10.2
unnamed: D11.2 (A), R11.2
unnamed: D12.2 (A), R12.2
unnamed: D13.2 (A), R13.2
unnamed: D14.2 (A), R19.2
unnamed: D15.2 (A), R20.2
unnamed: D16.2 (A), R21.2
unnamed: D17.2 (A), R22.2
unnamed: D18.2 (A), R23.2
unnamed: D19.2 (A), R39.2
unnamed: IC2.1 (VBB), R36.2
unnamed: J4.2, JP3.2
unnamed: JP4.2, R38.2
unnamed: R31.2, R32.1, R35.2

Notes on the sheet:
5V Active High Inputs
K-LINE
CAN
12V Active High Inputs (Level Shifters)
Speed Sensor Supply
Relay Drivers
Analog Signals
Voltage Supply
NUCLEO
can DNP LED to make signals 5 V
5V Active Low Inputs (Inverting Level Shifters)
Engine Cluster Connector
